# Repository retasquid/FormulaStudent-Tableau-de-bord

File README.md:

# 🏎️ PROJET FORMULA STUDENT - Système d'Affichage Temps Réel

Je suis fier de vous présenter notre travail réalisé dans le cadre du projet Formula Student à l'IUT Lyon 1 Villeurbanne Gratte-Ciel !

# 📍 Contexte :
Dans cette compétition automobile étudiante, plusieurs spécialités et groupes collaborent pour concevoir un véhicule de course. Matthia Pretotto et moi avons travaillé sur le système d'affichage des données du véhicule.

# ⚙️ Objectif du projet :
Développer un système capable d'acquérir, traiter et afficher en temps réel les données du tableau de bord via le bus CAN de la voiture de course.

# 📊 Fonctionnalités implémentées :
• Vitesse instantanée du véhicule
• Régime moteur (RPM)
• Heure actuelle
• Tension batterie
• Position GPS du véhicule

# 🛠️ Technologies employées :
Le projet se base sur un microcontrôleur 8 bits PIC18F27Q84 et un transceiver CAN pour interfacer le bus CAN. Le software a été réalisé en C depuis l'IDE MPLABX avec le plugin MCC pour simplifier la configuration des périphériques. Nous avons également conçu la carte électronique puis nous l'avons fait imprimer par un professionnel.

# 💡 Défis techniques relevés :
Les contraintes principales du projet étaient de réussir à rafraîchir rapidement l'écran malgré les limitations du microcontrôleur PIC et d'assurer une réception fiable des données provenant du bus CAN. Pour ce faire, nous avons développé des bibliothèques optimisées pour interagir efficacement avec le bus CAN et accélérer le calcul des jauges de l'écran, atteignant ainsi un taux de rafraîchissement d'environ 3Hz.

Merci à Mr. Ismael Bakiri et Mr. Anthony Chaussat pour leur encadrement et leur soutien tout au long de ce projet.

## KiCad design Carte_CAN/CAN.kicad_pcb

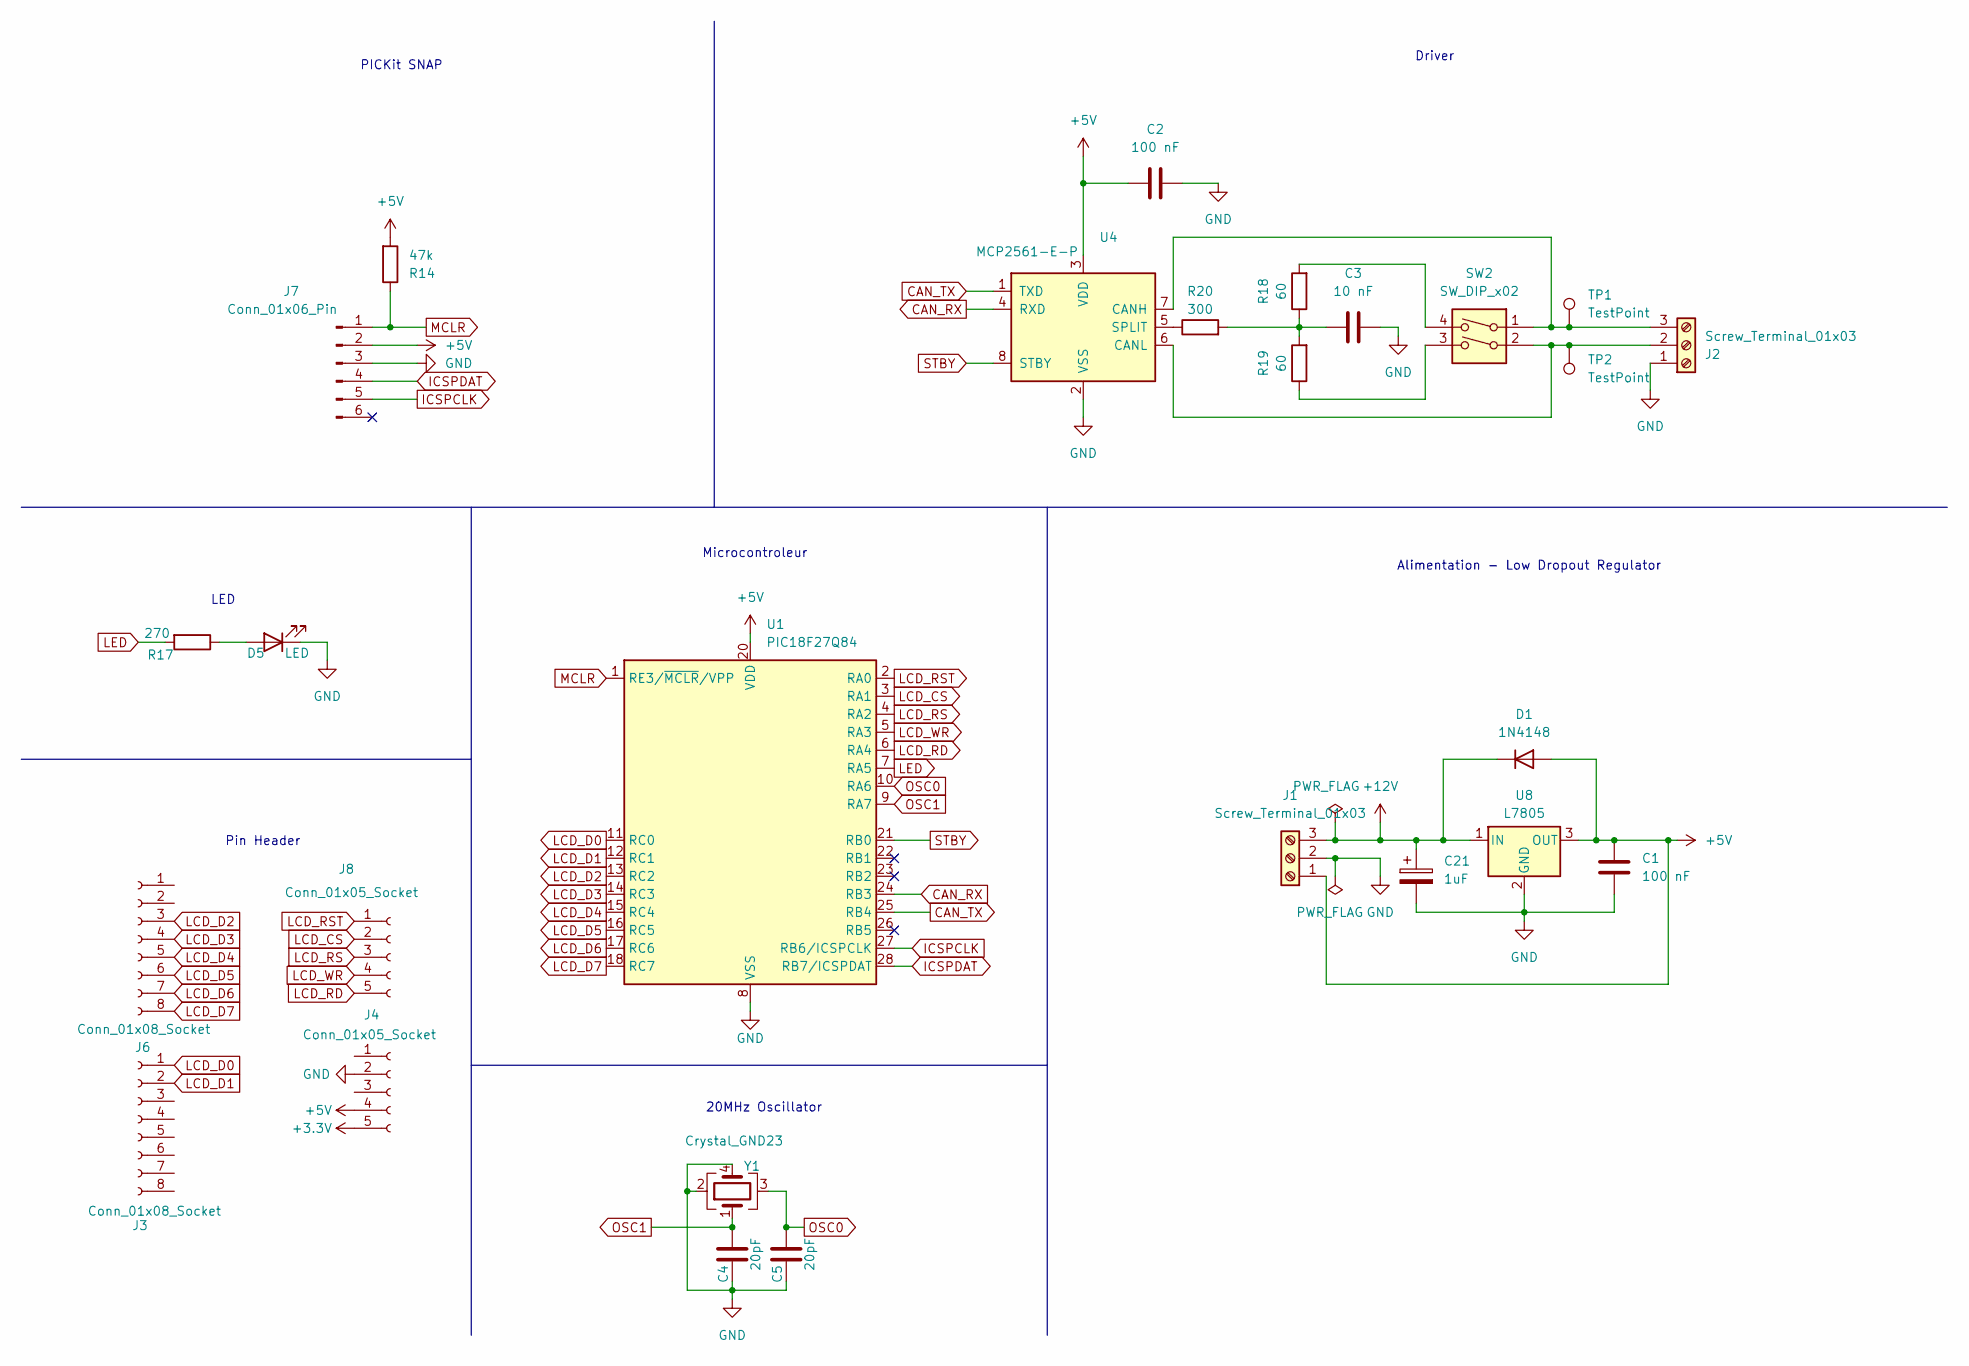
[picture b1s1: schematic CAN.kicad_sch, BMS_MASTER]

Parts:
C1, C2: 100 nF; C_Disc_D4.7mm_W2.5mm_P5.00mm
C3: 10 nF; C_Disc_D4.7mm_W2.5mm_P5.00mm
C4, C5: 20pF; C_0603_1608Metric
C21: 1uF; CP_Radial_D6.3mm_P2.50mm
D1: 1N4148; D_DO-35_SOD27_P7.62mm_Horizontal
D5: LED; LED_D5.0mm
J1, J2: Screw_Terminal_01x03; Bornier_1x03_L15mm_W7.5mm_P5.00mm
J3, J6: Conn_01x08_Socket; PinHeader_1x08_P2.54mm_Vertical
J4, J8: Conn_01x05_Socket; PinHeader_1x05_P2.54mm_Vertical
J7: Conn_01x06_Pin; PinHeader_1x06_P2.54mm_Vertical
R14: 47k; R_Axial_DIN0207_L6.3mm_D2.5mm_P10.16mm_Horizontal
R17: 270; R_Axial_DIN0207_L6.3mm_D2.5mm_P10.16mm_Horizontal
R18, R19: 60; R_Axial_DIN0207_L6.3mm_D2.5mm_P10.16mm_Horizontal
R20: 300; R_Axial_DIN0207_L6.3mm_D2.5mm_P10.16mm_Horizontal
SW2: SW_DIP_x02; SW_DIP_SPSTx02_Slide_7.5x7.01mm_W7.62mm_P2.54mm_LowProfile
TP1, TP2: TestPoint; TestPoint_Loop_D2.50mm_Drill1.0mm
U1: PIC18F27Q84; DIP787W45P254L3556H508Q28
U4: MCP2561-E-P; DIP-8_W7.62mm_LongPads
U8: L7805; TO255P1040X460X1968-3
Y1: Crystal_GND23; Crystal_SMD_3225-4Pin_3.2x2.5mm

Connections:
+3.3V: J4.5
+5V: C1.1, C2.1, D1.2 (A), J1.1, J4.4, J7.2, R14.2, U1.20 (VDD), U4.3 (VDD), U8.3 (OUT)
+12V: C21.1, D1.1 (K), J1.3, U8.1 (IN)
CAN_RX: U1.24 (RB3), U4.4 (RXD)
CAN_TX: U1.25 (RB4), U4.1 (TXD)
GND: C1.2, C2.2, C3.2, C4.2, C5.2, C21.2, D5.1 (K), J1.2, J2.1, J4.2, J7.3, U1.8 (VSS), U1.19 (VSS), U4.2 (VSS), U8.2 (GND), Y1.2, Y1.4
ICSPCLK: J7.5, U1.27 (RB6/ICSPCLK)
ICSPDAT: J7.4, U1.28 (RB7/ICSPDAT)
LCD_CS: J8.2, U1.3 (RA1)
LCD_D0: J3.1, U1.11 (RC0)
LCD_D1: J3.2, U1.12 (RC1)
LCD_D2: J6.3, U1.13 (RC2)
LCD_D3: J6.4, U1.14 (RC3)
LCD_D4: J6.5, U1.15 (RC4)
LCD_D5: J6.6, U1.16 (RC5)
LCD_D6: J6.7, U1.17 (RC6)
LCD_D7: J6.8, U1.18 (RC7)
LCD_RD: J8.5, U1.6 (RA4)
LCD_RS: J8.3, U1.4 (RA2)
LCD_RST: J8.1, U1.2 (RA0)
LCD_WR: J8.4, U1.5 (RA3)
LED: R17.2, U1.7 (RA5)
MCLR: J7.1, R14.1, U1.1 (RE3/~MCLR/VPP)
unnamed: C3.1, R18.1, R19.2, R20.2
unnamed: D5.2 (A), R17.1
unnamed: J2.2, SW2.2, TP2.1, U4.6 (CANL)
unnamed: J2.3, SW2.1, TP1.1, U4.7 (CANH)
unnamed: R18.2, SW2.4
unnamed: R19.1, SW2.3
unnamed: R20.1, U4.5 (SPLIT)
OSC0: C5.1, U1.10 (RA6), Y1.3
OSC1: C4.1, U1.9 (RA7), Y1.1
STBY: U1.21 (RB0), U4.8 (STBY)

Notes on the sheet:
Microcontroleur
LED
Alimentation - Low Dropout Regulator
Driver
PICKit SNAP
Pin Header
20MHz Oscillator

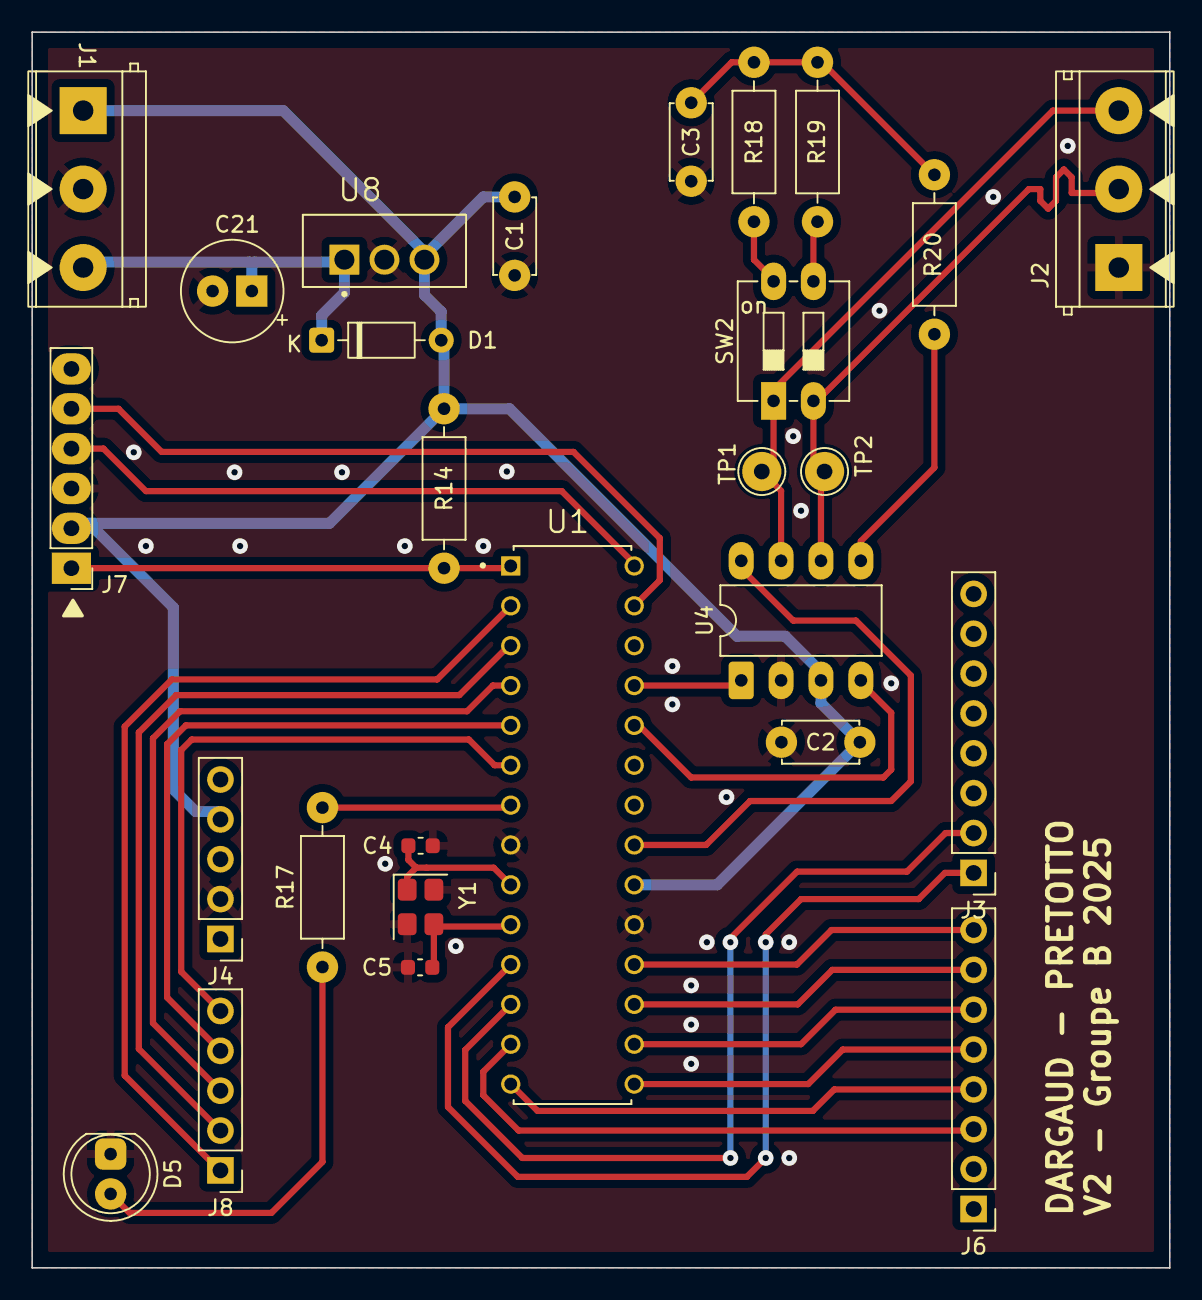
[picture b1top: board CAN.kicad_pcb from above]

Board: 2 copper layers, 72.5 x 78.8 mm, 27 parts (0 on the bottom side), 32 nets.

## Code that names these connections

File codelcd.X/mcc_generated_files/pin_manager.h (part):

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// get/set LCD_RST aliases
#define LCD_RST_TRIS                 TRISAbits.TRISA0
#define LCD_RST_LAT                  LATAbits.LATA0
#define LCD_RST_PORT                 PORTAbits.RA0
#define LCD_RST_WPU                  WPUAbits.WPUA0
#define LCD_RST_OD                   ODCONAbits.ODCA0
#define LCD_RST_ANS                  ANSELAbits.ANSELA0
#define LCD_RST_SetHigh()            do { LATAbits.LATA0 = 1; } while(0)
#define LCD_RST_SetLow()             do { LATAbits.LATA0 = 0; } while(0)
#define LCD_RST_Toggle()             do { LATAbits.LATA0 = ~LATAbits.LATA0; } while(0)
#define LCD_RST_GetValue()           PORTAbits.RA0
#define LCD_RST_SetDigitalInput()    do { TRISAbits.TRISA0 = 1; } while(0)
#define LCD_RST_SetDigitalOutput()   do { TRISAbits.TRISA0 = 0; } while(0)
#define LCD_RST_SetPullup()          do { WPUAbits.WPUA0 = 1; } while(0)
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// get/set LCD_CS aliases
#define LCD_CS_TRIS                 TRISAbits.TRISA1
#define LCD_CS_LAT                  LATAbits.LATA1
#define LCD_CS_PORT                 PORTAbits.RA1
#define LCD_CS_WPU                  WPUAbits.WPUA1
#define LCD_CS_OD                   ODCONAbits.ODCA1
#define LCD_CS_ANS                  ANSELAbits.ANSELA1
#define LCD_CS_SetHigh()            do { LATAbits.LATA1 = 1; } while(0)
#define LCD_CS_SetLow()             do { LATAbits.LATA1 = 0; } while(0)
#define LCD_CS_Toggle()             do { LATAbits.LATA1 = ~LATAbits.LATA1; } while(0)
#define LCD_CS_GetValue()           PORTAbits.RA1
#define LCD_CS_SetDigitalInput()    do { TRISAbits.TRISA1 = 1; } while(0)
#define LCD_CS_SetDigitalOutput()   do { TRISAbits.TRISA1 = 0; } while(0)
#define LCD_CS_SetPullup()          do { WPUAbits.WPUA1 = 1; } while(0)
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// get/set LCD_RS aliases
#define LCD_RS_TRIS                 TRISAbits.TRISA2
#define LCD_RS_LAT                  LATAbits.LATA2
#define LCD_RS_PORT                 PORTAbits.RA2
#define LCD_RS_WPU                  WPUAbits.WPUA2
#define LCD_RS_OD                   ODCONAbits.ODCA2
#define LCD_RS_ANS                  ANSELAbits.ANSELA2
#define LCD_RS_SetHigh()            do { LATAbits.LATA2 = 1; } while(0)
#define LCD_RS_SetLow()             do { LATAbits.LATA2 = 0; } while(0)
#define LCD_RS_Toggle()             do { LATAbits.LATA2 = ~LATAbits.LATA2; } while(0)
#define LCD_RS_GetValue()           PORTAbits.RA2
#define LCD_RS_SetDigitalInput()    do { TRISAbits.TRISA2 = 1; } while(0)
#define LCD_RS_SetDigitalOutput()   do { TRISAbits.TRISA2 = 0; } while(0)
#define LCD_RS_SetPullup()          do { WPUAbits.WPUA2 = 1; } while(0)
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// get/set LCD_WR aliases
#define LCD_WR_TRIS                 TRISAbits.TRISA3
#define LCD_WR_LAT                  LATAbits.LATA3
#define LCD_WR_PORT                 PORTAbits.RA3
#define LCD_WR_WPU                  WPUAbits.WPUA3
#define LCD_WR_OD                   ODCONAbits.ODCA3
#define LCD_WR_ANS                  ANSELAbits.ANSELA3
#define LCD_WR_SetHigh()            do { LATAbits.LATA3 = 1; } while(0)
#define LCD_WR_SetLow()             do { LATAbits.LATA3 = 0; } while(0)
#define LCD_WR_Toggle()             do { LATAbits.LATA3 = ~LATAbits.LATA3; } while(0)
#define LCD_WR_GetValue()           PORTAbits.RA3
#define LCD_WR_SetDigitalInput()    do { TRISAbits.TRISA3 = 1; } while(0)
#define LCD_WR_SetDigitalOutput()   do { TRISAbits.TRISA3 = 0; } while(0)
#define LCD_WR_SetPullup()          do { WPUAbits.WPUA3 = 1; } while(0)
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// get/set LCD_RD aliases
#define LCD_RD_TRIS                 TRISAbits.TRISA4
#define LCD_RD_LAT                  LATAbits.LATA4
#define LCD_RD_PORT                 PORTAbits.RA4
#define LCD_RD_WPU                  WPUAbits.WPUA4
#define LCD_RD_OD                   ODCONAbits.ODCA4
#define LCD_RD_ANS                  ANSELAbits.ANSELA4
#define LCD_RD_SetHigh()            do { LATAbits.LATA4 = 1; } while(0)
#define LCD_RD_SetLow()             do { LATAbits.LATA4 = 0; } while(0)
#define LCD_RD_Toggle()             do { LATAbits.LATA4 = ~LATAbits.LATA4; } while(0)
#define LCD_RD_GetValue()           PORTAbits.RA4
#define LCD_RD_SetDigitalInput()    do { TRISAbits.TRISA4 = 1; } while(0)
#define LCD_RD_SetDigitalOutput()   do { TRISAbits.TRISA4 = 0; } while(0)
#define LCD_RD_SetPullup()          do { WPUAbits.WPUA4 = 1; } while(0)
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// get/set LED aliases
#define LED_TRIS                 TRISAbits.TRISA5
#define LED_LAT                  LATAbits.LATA5
#define LED_PORT                 PORTAbits.RA5
#define LED_WPU                  WPUAbits.WPUA5
#define LED_OD                   ODCONAbits.ODCA5
#define LED_ANS                  ANSELAbits.ANSELA5
#define LED_SetHigh()            do { LATAbits.LATA5 = 1; } while(0)
#define LED_SetLow()             do { LATAbits.LATA5 = 0; } while(0)
#define LED_Toggle()             do { LATAbits.LATA5 = ~LATAbits.LATA5; } while(0)
#define LED_GetValue()           PORTAbits.RA5
#define LED_SetDigitalInput()    do { TRISAbits.TRISA5 = 1; } while(0)
#define LED_SetDigitalOutput()   do { TRISAbits.TRISA5 = 0; } while(0)
#define LED_SetPullup()          do { WPUAbits.WPUA5 = 1; } while(0)
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// get/set STBY aliases
#define STBY_TRIS                 TRISBbits.TRISB0
#define STBY_LAT                  LATBbits.LATB0
#define STBY_PORT                 PORTBbits.RB0
#define STBY_WPU                  WPUBbits.WPUB0
#define STBY_OD                   ODCONBbits.ODCB0
#define STBY_ANS                  ANSELBbits.ANSELB0
#define STBY_SetHigh()            do { LATBbits.LATB0 = 1; } while(0)
#define STBY_SetLow()             do { LATBbits.LATB0 = 0; } while(0)
#define STBY_Toggle()             do { LATBbits.LATB0 = ~LATBbits.LATB0; } while(0)
#define STBY_GetValue()           PORTBbits.RB0
#define STBY_SetDigitalInput()    do { TRISBbits.TRISB0 = 1; } while(0)
#define STBY_SetDigitalOutput()   do { TRISBbits.TRISB0 = 0; } while(0)
#define STBY_SetPullup()          do { WPUBbits.WPUB0 = 1; } while(0)
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#define RB3_SetHigh()            do { LATBbits.LATB3 = 1; } while(0)
#define RB3_SetLow()             do { LATBbits.LATB3 = 0; } while(0)
#define RB3_Toggle()             do { LATBbits.LATB3 = ~LATBbits.LATB3; } while(0)
#define RB3_GetValue()              PORTBbits.RB3
#define RB3_SetDigitalInput()    do { TRISBbits.TRISB3 = 1; } while(0)
#define RB3_SetDigitalOutput()   do { TRISBbits.TRISB3 = 0; } while(0)
#define RB3_SetPullup()             do { WPUBbits.WPUB3 = 1; } while(0)
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#define RB4_SetHigh()            do { LATBbits.LATB4 = 1; } while(0)
#define RB4_SetLow()             do { LATBbits.LATB4 = 0; } while(0)
#define RB4_Toggle()             do { LATBbits.LATB4 = ~LATBbits.LATB4; } while(0)
#define RB4_GetValue()              PORTBbits.RB4
#define RB4_SetDigitalInput()    do { TRISBbits.TRISB4 = 1; } while(0)
#define RB4_SetDigitalOutput()   do { TRISBbits.TRISB4 = 0; } while(0)
#define RB4_SetPullup()             do { WPUBbits.WPUB4 = 1; } while(0)
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// get/set LCD_D0 aliases
#define LCD_D0_TRIS                 TRISCbits.TRISC0
#define LCD_D0_LAT                  LATCbits.LATC0
#define LCD_D0_PORT                 PORTCbits.RC0
#define LCD_D0_WPU                  WPUCbits.WPUC0
#define LCD_D0_OD                   ODCONCbits.ODCC0
#define LCD_D0_ANS                  ANSELCbits.ANSELC0
#define LCD_D0_SetHigh()            do { LATCbits.LATC0 = 1; } while(0)
#define LCD_D0_SetLow()             do { LATCbits.LATC0 = 0; } while(0)
#define LCD_D0_Toggle()             do { LATCbits.LATC0 = ~LATCbits.LATC0; } while(0)
#define LCD_D0_GetValue()           PORTCbits.RC0
#define LCD_D0_SetDigitalInput()    do { TRISCbits.TRISC0 = 1; } while(0)
#define LCD_D0_SetDigitalOutput()   do { TRISCbits.TRISC0 = 0; } while(0)
#define LCD_D0_SetPullup()          do { WPUCbits.WPUC0 = 1; } while(0)
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// get/set LCD_D1 aliases
#define LCD_D1_TRIS                 TRISCbits.TRISC1
#define LCD_D1_LAT                  LATCbits.LATC1
#define LCD_D1_PORT                 PORTCbits.RC1
#define LCD_D1_WPU                  WPUCbits.WPUC1
#define LCD_D1_OD                   ODCONCbits.ODCC1
#define LCD_D1_ANS                  ANSELCbits.ANSELC1
#define LCD_D1_SetHigh()            do { LATCbits.LATC1 = 1; } while(0)
#define LCD_D1_SetLow()             do { LATCbits.LATC1 = 0; } while(0)
#define LCD_D1_Toggle()             do { LATCbits.LATC1 = ~LATCbits.LATC1; } while(0)
#define LCD_D1_GetValue()           PORTCbits.RC1
#define LCD_D1_SetDigitalInput()    do { TRISCbits.TRISC1 = 1; } while(0)
#define LCD_D1_SetDigitalOutput()   do { TRISCbits.TRISC1 = 0; } while(0)
#define LCD_D1_SetPullup()          do { WPUCbits.WPUC1 = 1; } while(0)
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// get/set LCD_D2 aliases
#define LCD_D2_TRIS                 TRISCbits.TRISC2
#define LCD_D2_LAT                  LATCbits.LATC2
#define LCD_D2_PORT                 PORTCbits.RC2
#define LCD_D2_WPU                  WPUCbits.WPUC2
#define LCD_D2_OD                   ODCONCbits.ODCC2
#define LCD_D2_ANS                  ANSELCbits.ANSELC2
#define LCD_D2_SetHigh()            do { LATCbits.LATC2 = 1; } while(0)
#define LCD_D2_SetLow()             do { LATCbits.LATC2 = 0; } while(0)
#define LCD_D2_Toggle()             do { LATCbits.LATC2 = ~LATCbits.LATC2; } while(0)
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
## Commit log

2026-04-05 Revise README with project details and features
    Updated the README to provide detailed project context, objectives, features, technologies, and challenges.
2026-04-29 Added PCB files
2026-04-29 Added Main program
2026-04-29 added test program
2026-04-29 Added medias

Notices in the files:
codelcd.X/mcc_generated_files/pin_manager.h:
(c) 2018 Microchip Technology Inc. and its subsidiaries.
